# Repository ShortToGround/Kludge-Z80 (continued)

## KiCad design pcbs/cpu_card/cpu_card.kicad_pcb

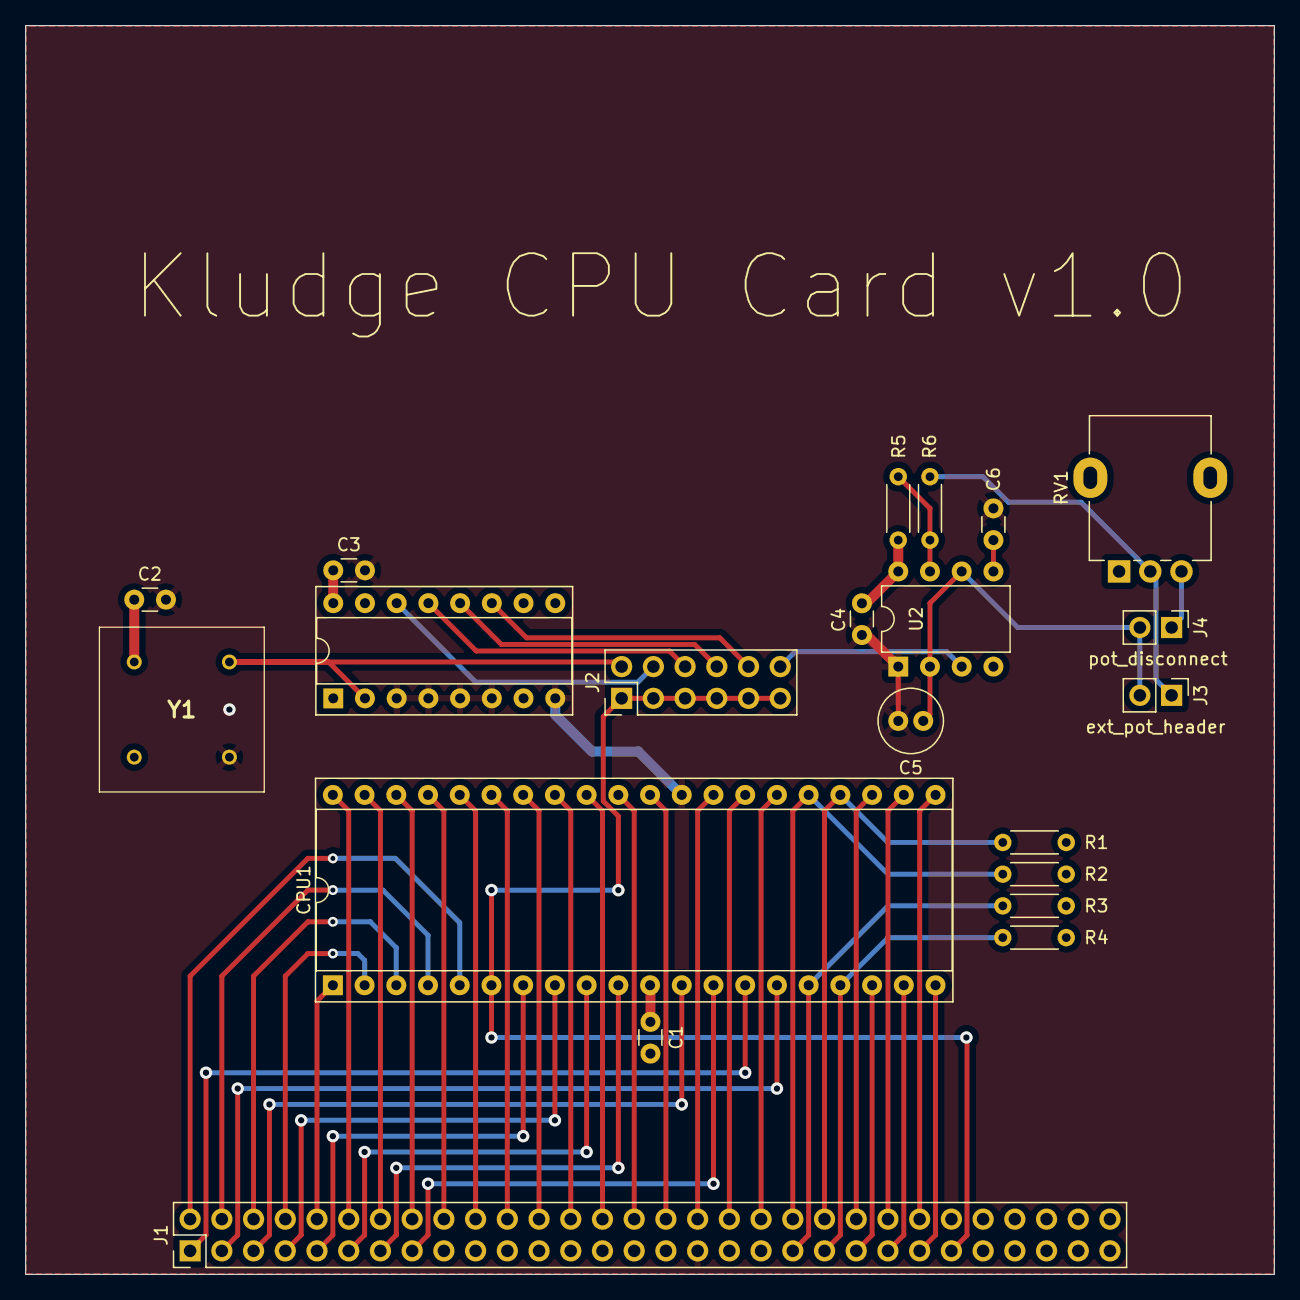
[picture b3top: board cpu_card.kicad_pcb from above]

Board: 4 copper layers, 100.0 x 100.0 mm, 21 parts (0 on the bottom side), 51 nets.

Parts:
C1, C2, C3, C4: 100 nF; C_Disc_D3.0mm_W1.6mm_P2.54mm
C5: 1 uF; C_Radial_D5.0mm_H11.0mm_P2.00mm
C6: 0.01 uF; C_Disc_D3.0mm_W1.6mm_P2.54mm
CPU1: Z80CPU; DIP-40_W15.24mm_Socket
J1: Conn1; PinHeader_2x30_P2.54mm_Vertical
J2: osc_header; PinHeader_2x06_P2.54mm_Vertical
J3: ext_pot_header; PinHeader_1x02_P2.54mm_Vertical
J4: pot_disconnect; PinHeader_1x02_P2.54mm_Vertical
R1, R2, R3, R4: 3.3K; R_Axial_DIN0204_L3.6mm_D1.6mm_P5.08mm_Horizontal
R5, R6: 1K; R_Axial_DIN0204_L3.6mm_D1.6mm_P5.08mm_Horizontal
RV1: 1M; Potentiometer_Alpha_RD901F-40-00D_Single_Vertical
U1: 74LS161; DIP-16_W7.62mm_Socket
U2: ICM7555xP; DIP-8_W7.62mm
Y1: ECS-2100AX-200

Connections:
/1.25 MHz: J2.10, U1.11 (Q3)
/2.5 MHz: J2.8, U1.12 (Q2)
/5 MHz: J2.6, U1.13 (Q1)
/10 MHz: J2.4, U1.14 (Q0)
/A0: CPU1.30 (A0), J1.32
/A1: CPU1.31 (A1), J1.30
/A2: CPU1.32 (A2), J1.28
/A3: CPU1.33 (A3), J1.26
/A4: CPU1.34 (A4), J1.24
/A5: CPU1.35 (A5), J1.22
/A6: CPU1.36 (A6), J1.20
/A7: CPU1.37 (A7), J1.18
/A8: CPU1.38 (A8), J1.16
/A9: CPU1.39 (A9), J1.14
/A10: CPU1.40 (A10), J1.12
/A11: CPU1.1 (A11), J1.10
/A12: CPU1.2 (A12), J1.8
/A13: CPU1.3 (A13), J1.6
/A14: CPU1.4 (A14), J1.4
/A15: CPU1.5 (A15), J1.2
/D0: CPU1.14 (D0), J1.1
/D1: CPU1.15 (D1), J1.3
/D2: CPU1.12 (D2), J1.5
/D3: CPU1.8 (D3), J1.7
/D4: CPU1.7 (D4), J1.9
/D5: CPU1.9 (D5), J1.11
/D6: CPU1.10 (D6), J1.13
/D7: CPU1.13 (D7), J1.15
BUSAK: CPU1.23 (~BUSACK), J1.44
BUSRQ: CPU1.25 (~BUSRQ), J1.40, R2.1
GND: C1.2, C2.2, C3.2, C4.2, C5.2, C6.2, CPU1.29 (GND), J1.33, U1.3 (D0), U1.4 (D1), U1.5 (D2), U1.6 (D3), U1.8 (GND), U2.1 (GND), Y1.4 (GROUND)
HALT: CPU1.18 (~HALT), J1.43
INT: CPU1.16 (~INT), J1.39, R3.1
IOREQ: CPU1.20 (~IORQ), J1.47
M1: CPU1.27 (~M1), J1.36
MREQ: CPU1.19 (~MREQ), J1.45
NMI: CPU1.17 (~NMI), J1.41, R4.1
unnamed: J3.1, R6.2, RV1.2
unnamed: C5.1, J3.2, J4.2, U2.2 (TR), U2.6 (THR)
unnamed: J4.1, RV1.3
unnamed: C6.1, U2.5 (CV)
unnamed: R5.2, R6.1, U2.7 (DIS)
OSC: J2.2, U1.2 (CP), Y1.5 (OUTPUT)
OSC_ADJ: J2.12, U2.3 (Q)
RD: CPU1.21 (~RD), J1.48
RESET: CPU1.26 (~RESET), J1.38
RFSH: CPU1.28 (~RFSH), J1.34
SYSCLK: CPU1.6 (~CLK), J1.49, J2.1, J2.3, J2.5, J2.7, J2.9, J2.11
VCC: C1.1, C2.1, C3.1, C4.1, CPU1.11 (VCC), J1.35, R1.2, R2.2, R3.2, R4.2, R5.1, U1.1 (~MR), U1.7 (CEP), U1.9 (~PE), U1.10 (CET), U1.15 (TC), U1.16 (VCC), U2.4 (R), U2.8 (VCC), Y1.8 (+5V_DC)
WAIT: CPU1.24 (~WAIT), J1.42, R1.1
WR: CPU1.22 (~WR), J1.46

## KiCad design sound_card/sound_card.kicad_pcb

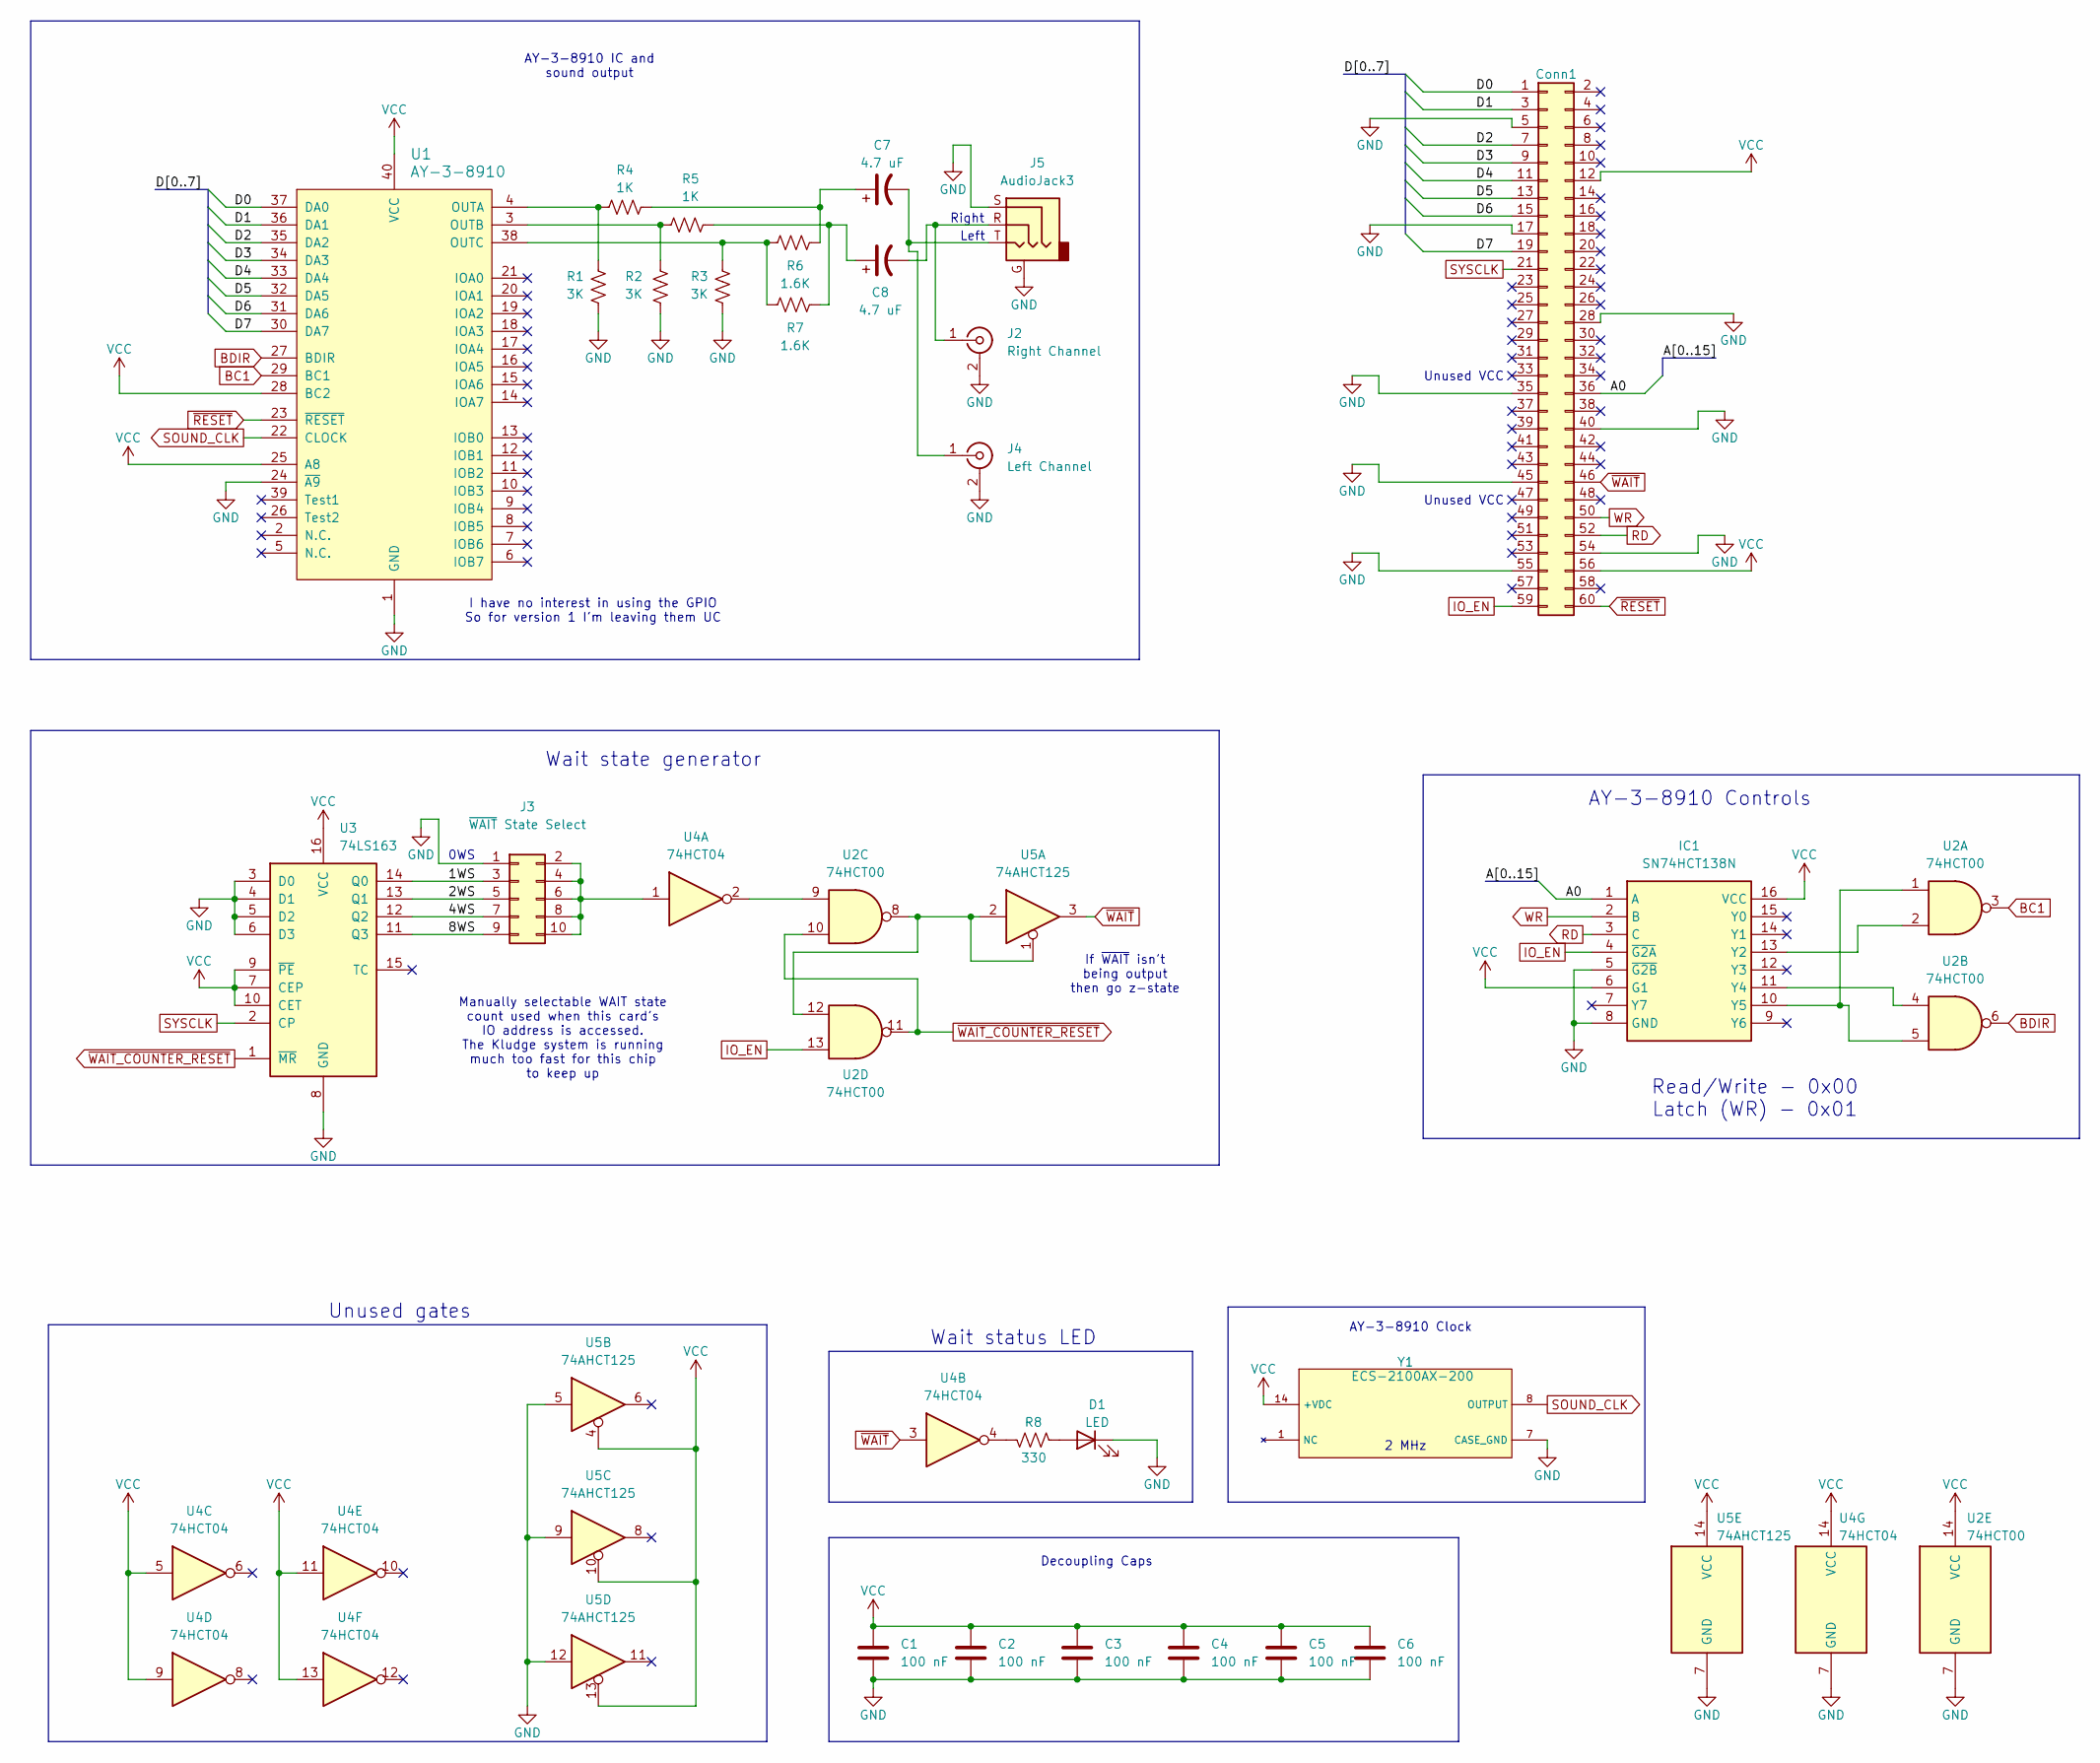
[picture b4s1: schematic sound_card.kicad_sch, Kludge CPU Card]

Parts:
C1, C2, C3, C4, C5, C6: 100 nF; C_Disc_D3.0mm_W1.6mm_P2.50mm
C7, C8: 4.7 uF; CP_Radial_D6.3mm_P2.50mm
D1: LED; LED_D3.0mm
IC1: SN74HCT138N; DIP-16_W7.62mm_Socket; Mouser Part Number 595-SN74HCT138N
J1: Conn1; PinHeader_2x30_P2.54mm_Vertical
J2: Right Channel; RCJ-04X_CUD
J3: ~{WAIT} State Select; PinHeader_2x05_P2.54mm_Vertical
J4: Left Channel; RCJ-04X_CUD
J5: AudioJack3; Jack_3.5mm_CUI_SJ1-3523N_Horizontal
R1, R2, R3: 3K; R_Axial_DIN0207_L6.3mm_D2.5mm_P10.16mm_Horizontal
R4, R5: 1K; R_Axial_DIN0207_L6.3mm_D2.5mm_P10.16mm_Horizontal
R6, R7: 1.6K; R_Axial_DIN0207_L6.3mm_D2.5mm_P10.16mm_Horizontal
R8: 330; R_Axial_DIN0207_L6.3mm_D2.5mm_P10.16mm_Horizontal
U1: AY-3-8910
U2: 74HCT00; DIP-14_W7.62mm_Socket
U3: 74LS163; DIP-16_W7.62mm_Socket
U4: 74HCT04; DIP-14_W7.62mm_Socket
U5: 74AHCT125; DIP-14_W7.62mm_Socket
Y1: ECS-2100AX-200; OSC_ECS-100AX-018; Manufacturer_Part_Number ECS-2100AX-100

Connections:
/1WS: J3.3, U3.14 (Q0)
/2WS: J3.5, U3.13 (Q1)
/4WS: J3.7, U3.12 (Q2)
/8WS: J3.9, U3.11 (Q3)
/A0: IC1.1 (A), J1.36
/D0: J1.1, U1.37 (DA0)
/D1: J1.3, U1.36 (DA1)
/D2: J1.7, U1.35 (DA2)
/D3: J1.9, U1.34 (DA3)
/D4: J1.11, U1.33 (DA4)
/D5: J1.13, U1.32 (DA5)
/D6: J1.15, U1.31 (DA6)
/D7: J1.19, U1.30 (DA7)
BC1: U1.29 (BC1), U2.3
BDIR: U1.27 (BDIR), U2.6
GND: C1.2, C2.2, C3.2, C4.2, C5.2, C6.2, D1.1 (K), IC1.5 (~G2B), IC1.8 (GND), J1.5, J1.17, J1.28, J1.35, J1.40, J1.45, J1.54, J1.55, J2.2 (Ext), J3.1, J4.2 (Ext), J5.G, J5.S, R1.1, R2.1, R3.1, U1.1 (GND), U1.24 (~A9), U2.7 (GND), U3.3 (D0), U3.4 (D1), U3.5 (D2), U3.6 (D3), U3.8 (GND), U4.7 (GND), U5.5, U5.7 (GND), U5.9, U5.12, Y1.7 (CASE_GND)
IO_EN: IC1.4 (~G2A), J1.59, U2.13
unnamed: C7.1, R4.2, R6.2
unnamed: C8.1, R5.2, R7.2
unnamed: D1.2 (A), R8.1
unnamed: IC1.13 (Y2), U2.2
unnamed: IC1.11 (Y4), U2.4
unnamed: IC1.10 (Y5), U2.1, U2.5
unnamed: C8.2, J2.1 (In), J5.R
unnamed: J3.2, J3.4, J3.6, J3.8, J3.10, U4.1
unnamed: C7.2, J4.1 (In), J5.T
unnamed: R8.2, U4.4
unnamed: R1.2, R4.1, U1.4 (OUTA)
unnamed: R2.2, R5.1, U1.3 (OUTB)
unnamed: R3.2, R6.1, R7.1, U1.38 (OUTC)
unnamed: U2.9, U4.2
unnamed: U2.8, U2.12, U5.1, U5.2
RD: IC1.3 (C), J1.52
SOUND_CLK: U1.22 (CLOCK), Y1.8 (OUTPUT)
SYSCLK: J1.21, U3.2 (CP)
VCC: C1.1, C2.1, C3.1, C4.1, C5.1, C6.1, IC1.6 (G1), IC1.16 (VCC), J1.12, J1.56, U1.25 (A8), U1.28 (BC2), U1.40 (VCC), U2.14 (VCC), U3.7 (CEP), U3.9 (~PE), U3.10 (CET), U3.16 (VCC), U4.5, U4.9, U4.11, U4.13, U4.14 (VCC), U5.4, U5.10, U5.13, U5.14 (VCC), Y1.14 (+VDC)
WR: IC1.2 (B), J1.50
~RESET: J1.60, U1.23 (~RESET)
~WAIT_COUNTER_RESET: U2.10, U2.11, U3.1 (~MR)
~WAIT: J1.46, U4.3, U5.3

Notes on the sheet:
Left
0WS
AY-3-8910 Controls
Wait state generator
I have no interest in using the GPIO So for version 1 I'm leaving them UC
AY-3-8910 IC and sound output
Unused VCC
Unused gates
Right
Read/Write - 0x00 Latch (WR) - 0x01
AY-3-8910 Clock
If ~{WAIT} isn't being output then go z-state
Manually selectable WAIT state count used when this card's IO address is accessed. The Kludge system is running much too fast for this chip to keep up
2 MHz
Decoupling Caps
Wait status LED

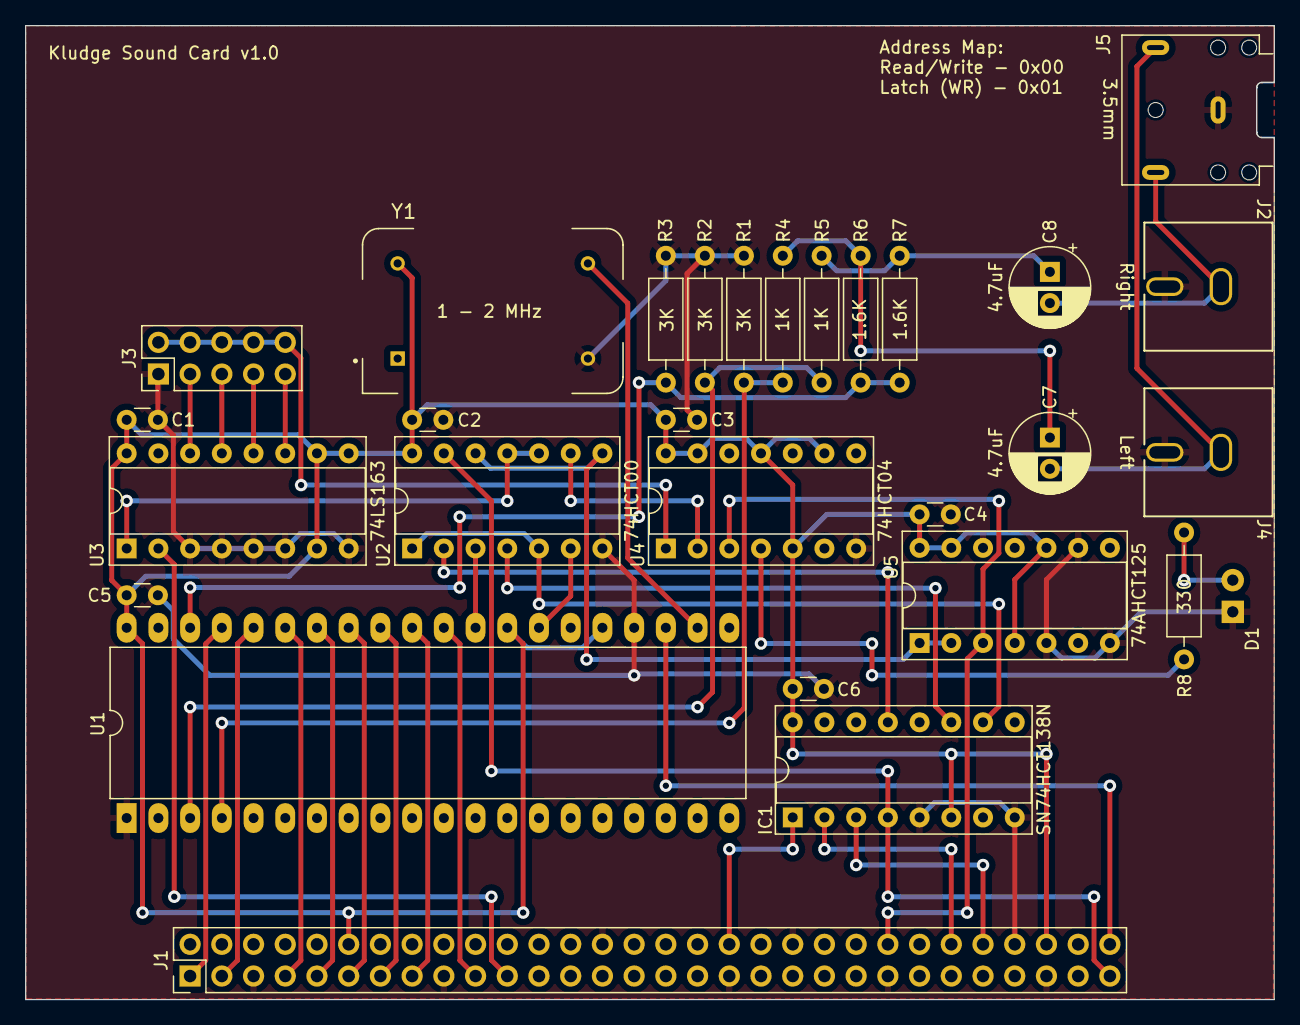
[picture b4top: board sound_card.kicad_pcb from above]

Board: 2 copper layers, 100.0 x 78.0 mm, 29 parts (0 on the bottom side), 40 nets.
